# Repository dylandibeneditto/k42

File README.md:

<h1 align="center">K42</h1>

### Features
- **Wireless** BLE
- Onboard **Haptic Feedback**
- **Aluminum** Plate and Rotary Knobs
- 2x **Rotary Encoders** (per half)
- 2x SSD1306 **OLED** (per half)
- Reversible PCB
- **Hotswappable Choc** switches

### Purchasing
- Planning on a **DIY kit** for $150

> **One prototype for me cost ~$250**, so buying the kit saves a significant amount

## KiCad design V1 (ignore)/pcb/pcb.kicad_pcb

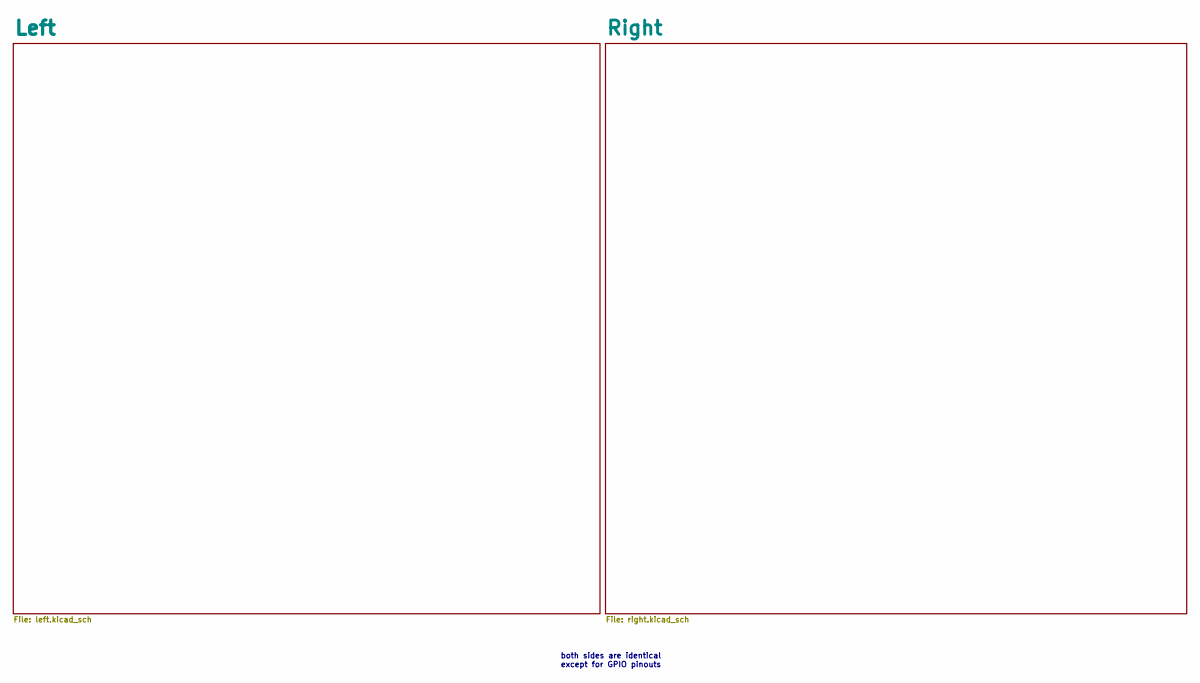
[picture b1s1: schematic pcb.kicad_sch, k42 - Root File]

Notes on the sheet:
both sides are identical except for GPIO pinouts

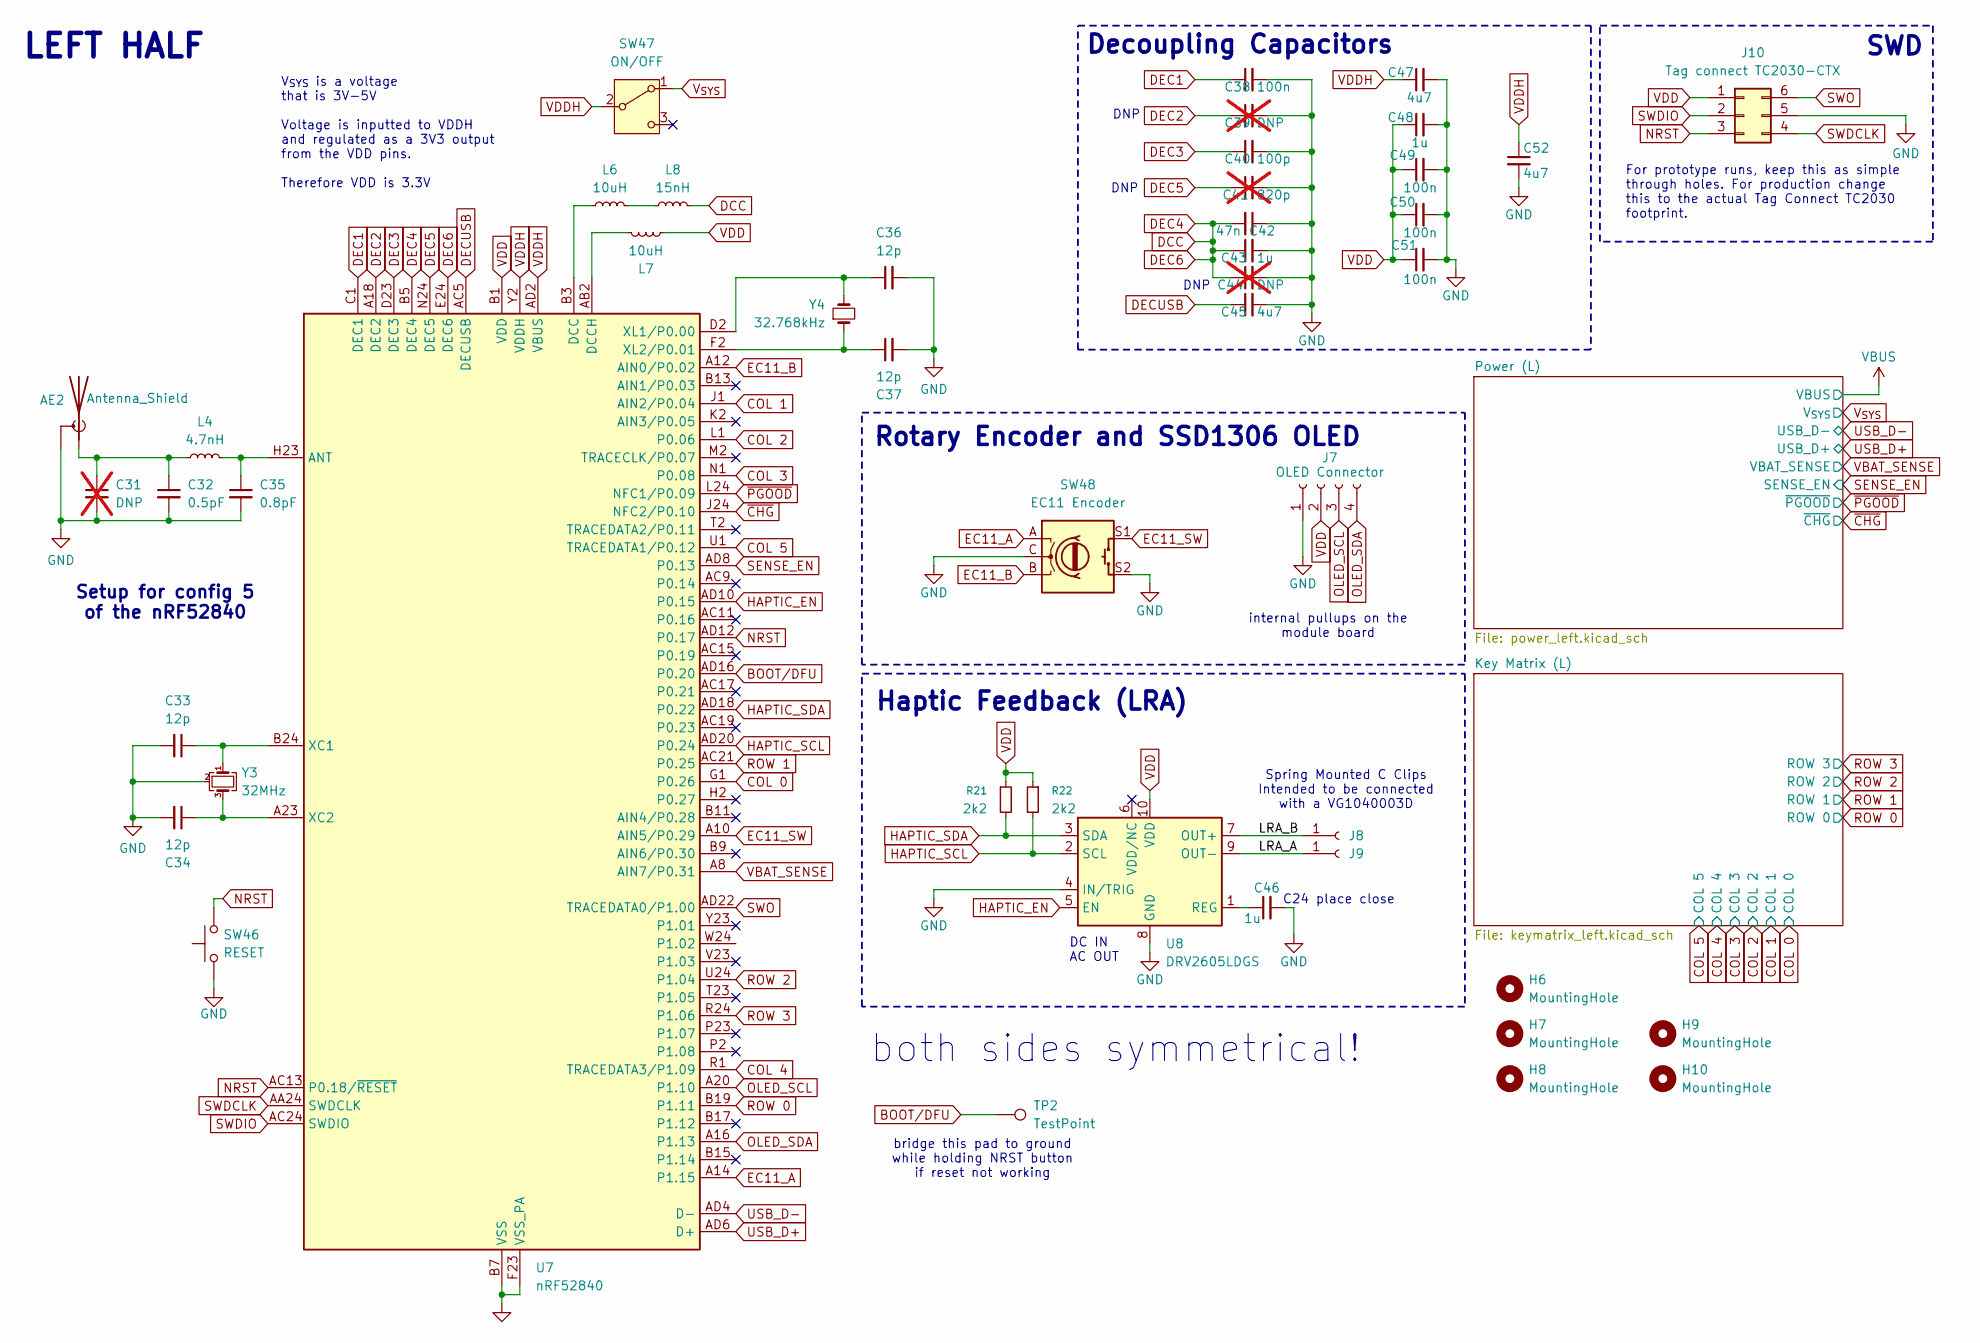
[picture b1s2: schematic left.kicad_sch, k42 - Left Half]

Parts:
AE2: Antenna_Shield; BLE_ANTENNA
C31, C39, C44: DNP; C_0402_1005Metric; not fitted
C32: 0.5pF; C_0402_1005Metric; LCSC Part Number C1544
C33, C34, C36, C37: 12p; C_0402_1005Metric; LCSC Part Number C1547
C35: 0.8pF; C_0402_1005Metric; LCSC Part Number C88902
C38, C49, C50, C51: 100n; C_0402_1005Metric; LCSC Part Number C1525
C40: 100p; C_0402_1005Metric; LCSC Part Number C1546
C41: 820p; C_0402_1005Metric; LCSC Part Number C1543; not fitted
C42: 47n; C_0402_1005Metric; LCSC Part Number C82219
C43, C46, C48: 1u; C_0603_1608Metric; LCSC Part Number C15849
C45, C47, C52: 4u7; C_0805_2012Metric; LCSC Part Number C1779
H6, H7, H8, H9, H10: MountingHole; MountingHole_2.2mm_M2
J7: OLED Connector; OLED
J8, J9: Conn_01x01_Socket; TE_2199248-6; LCSC Part Number C3308715
J10: Tag connect TC2030-CTX; PinHeader_2x03_P2.54mm_Vertical
L4: 4.7nH; L_0402_1005Metric; LCSC Part Number C86065
L6, L7: 10uH; L_0603_1608Metric; LCSC Part Number C1035
L8: 15nH; L_0402_1005Metric; LCSC Part Number C86059
R21, R22: 2k2; R_0402_1005Metric; LCSC Part Number C25879
SW46: RESET; SW_Push_SPST_NO_Alps_SKRK; LCSC Part Number C720477
SW47: ON/OFF; SW_SPDT_CK_JS102011SAQN; LCSC Part Number C49023767
SW48: EC11 Encoder; RotaryEncoder_Alps_EC11E-Switch_Vertical_H20mm_MountingHoles
TP2: TestPoint; TestPoint_Pad_2.0x2.0mm
U7: nRF52840; Nordic_AQFN-73-1EP_7x7mm_P0.5mm; LCSC Part Number C190794
U8: DRV2605LDGS; VSSOP-10_3x3mm_P0.5mm; LCSC Part Number C527464
Y3: 32MHz; Crystal_SMD_3225-4Pin_3.2x2.5mm; LCSC Part Number C9009
Y4: 32.768kHz; Crystal_SMD_3215-2Pin_3.2x1.5mm; LCSC Part Number C32346

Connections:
/Left/LRA_A: J9.1 (Pin_1_1), U8.9 (OUT-)
/Left/LRA_B: J8.1 (1_1), U8.7 (OUT+)
BOOT/DFU: TP2.1 (1_1), U7.AD16 (P0.20); also elsewhere on the board
COL 0: U7.G1 (P0.26); also elsewhere on the board
COL 1: U7.J1 (AIN2/P0.04); also elsewhere on the board
COL 2: U7.L1 (P0.06); also elsewhere on the board
COL 3: U7.N1 (P0.08); also elsewhere on the board
COL 4: U7.R1 (TRACEDATA3/P1.09); also elsewhere on the board
COL 5: U7.U1 (TRACEDATA1/P0.12); also elsewhere on the board
DCC: C42.2, C43.1, C44.1, L8.2, U7.B5 (DEC4), U7.E24 (DEC6); also elsewhere on the board
DEC3: C40.1, U7.D23 (DEC3); also elsewhere on the board
DECUSB: C45.1, U7.AC5 (DECUSB); also elsewhere on the board
EC11_A: SW48.A, U7.A14 (P1.15); also elsewhere on the board
EC11_B: SW48.B, U7.A12 (AIN0/P0.02); also elsewhere on the board
EC11_SW: SW48.S1, U7.A10 (AIN5/P0.29); also elsewhere on the board
GND: AE2.2 (Shield), C31.2, C32.2, C33.2, C34.2, C35.2, C36.2, C37.2, C38.2, C39.2, C40.2, C41.2, C42.1, C43.2, C44.2, C45.2, C46.2, C47.2, C48.2, C49.2, C50.2, C51.2, C52.2, J7.1, J10.5, SW46.1, SW48.C, SW48.S2, U7.B7 (VSS), U7.EP (VSS), U7.F23 (VSS_PA), U8.4 (IN/TRIG), U8.8 (GND), Y3.2 (G), Y3.4 (G); also elsewhere on the board
HAPTIC_EN: U7.AD10 (P0.15), U8.5 (EN); also elsewhere on the board
HAPTIC_SCL: R22.2, U7.AD20 (P0.24), U8.2 (SCL); also elsewhere on the board
HAPTIC_SDA: R21.2, U7.AD18 (P0.22), U8.3 (SDA); also elsewhere on the board
NRST: J10.3, SW46.2, U7.AC13 (P0.18/~RESET), U7.AD12 (P0.17); also elsewhere on the board
unnamed: AE2.1 (A), C31.1, C32.1, L4.1
unnamed: L6.2, L8.1
unnamed: C35.1, L4.2, U7.H23 (ANT)
unnamed: L6.1, U7.B3 (DCC)
unnamed: L7.1, U7.AB2 (DCCH)
unnamed: C33.1, U7.B24 (XC1), Y3.1
unnamed: C34.1, U7.A23 (XC2), Y3.3
unnamed: C36.1, U7.D2 (XL1/P0.00), Y4.2
unnamed: C37.1, U7.F2 (XL2/P0.01), Y4.1
unnamed: C46.1, U8.1 (REG)
OLED_SCL: J7.3, U7.A20 (P1.10); also elsewhere on the board
OLED_SDA: J7.4, U7.A16 (P1.13); also elsewhere on the board
ROW 0: U7.B19 (P1.11); also elsewhere on the board
ROW 1: U7.AC21 (P0.25); also elsewhere on the board
ROW 2: U7.U24 (P1.04); also elsewhere on the board
ROW 3: U7.R24 (P1.06); also elsewhere on the board
SENSE_EN: U7.AD8 (P0.13); also elsewhere on the board
SWDCLK: J10.4, U7.AA24 (SWDCLK); also elsewhere on the board
SWDIO: J10.2, U7.AC24 (SWDIO); also elsewhere on the board
SWO: J10.6, U7.AD22 (TRACEDATA0/P1.00); also elsewhere on the board
USB_D+: U7.AD6 (D+); also elsewhere on the board
USB_D-: U7.AD4 (D-); also elsewhere on the board
VBAT_SENSE: U7.A8 (AIN7/P0.31); also elsewhere on the board
VDD: C48.1, C49.1, C50.1, C51.1, J7.2, J10.1, L7.2, R21.1, R22.1, U7.A22 (VDD), U7.AD14 (VDD), U7.AD23 (VDD), U7.B1 (VDD), U7.W1 (VDD), U8.10 (VDD); also elsewhere on the board
VDDH: C47.1, C52.1, SW47.2 (B), U7.AD2 (VBUS), U7.Y2 (VDDH); also elsewhere on the board
V_{SYS}: SW47.1 (A); also elsewhere on the board
~CHG: U7.J24 (NFC2/P0.10); also elsewhere on the board
~PGOOD: U7.L24 (NFC1/P0.09); also elsewhere on the board

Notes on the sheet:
DC IN AC OUT
DNP
LEFT HALF
For prototype runs, keep this as simple through holes. For production change this to the actual Tag Connect TC2030 footprint.
Spring Mounted C Clips Intended to be connected with a VG1040003D
bridge this pad to ground while holding NRST button if reset not working
internal pullups on the module board
V_{SYS} is a voltage that is 3V-5V Voltage is inputted to VDDH and regulated as a 3V3 output from the VDD pins. Therefore VDD is 3.3V
SWD
both sides symmetrical!
C24 place close
Decoupling Capacitors
Rotary Encoder and SSD1306 OLED
Haptic Feedback (LRA)
Setup for config 5 of the nRF52840

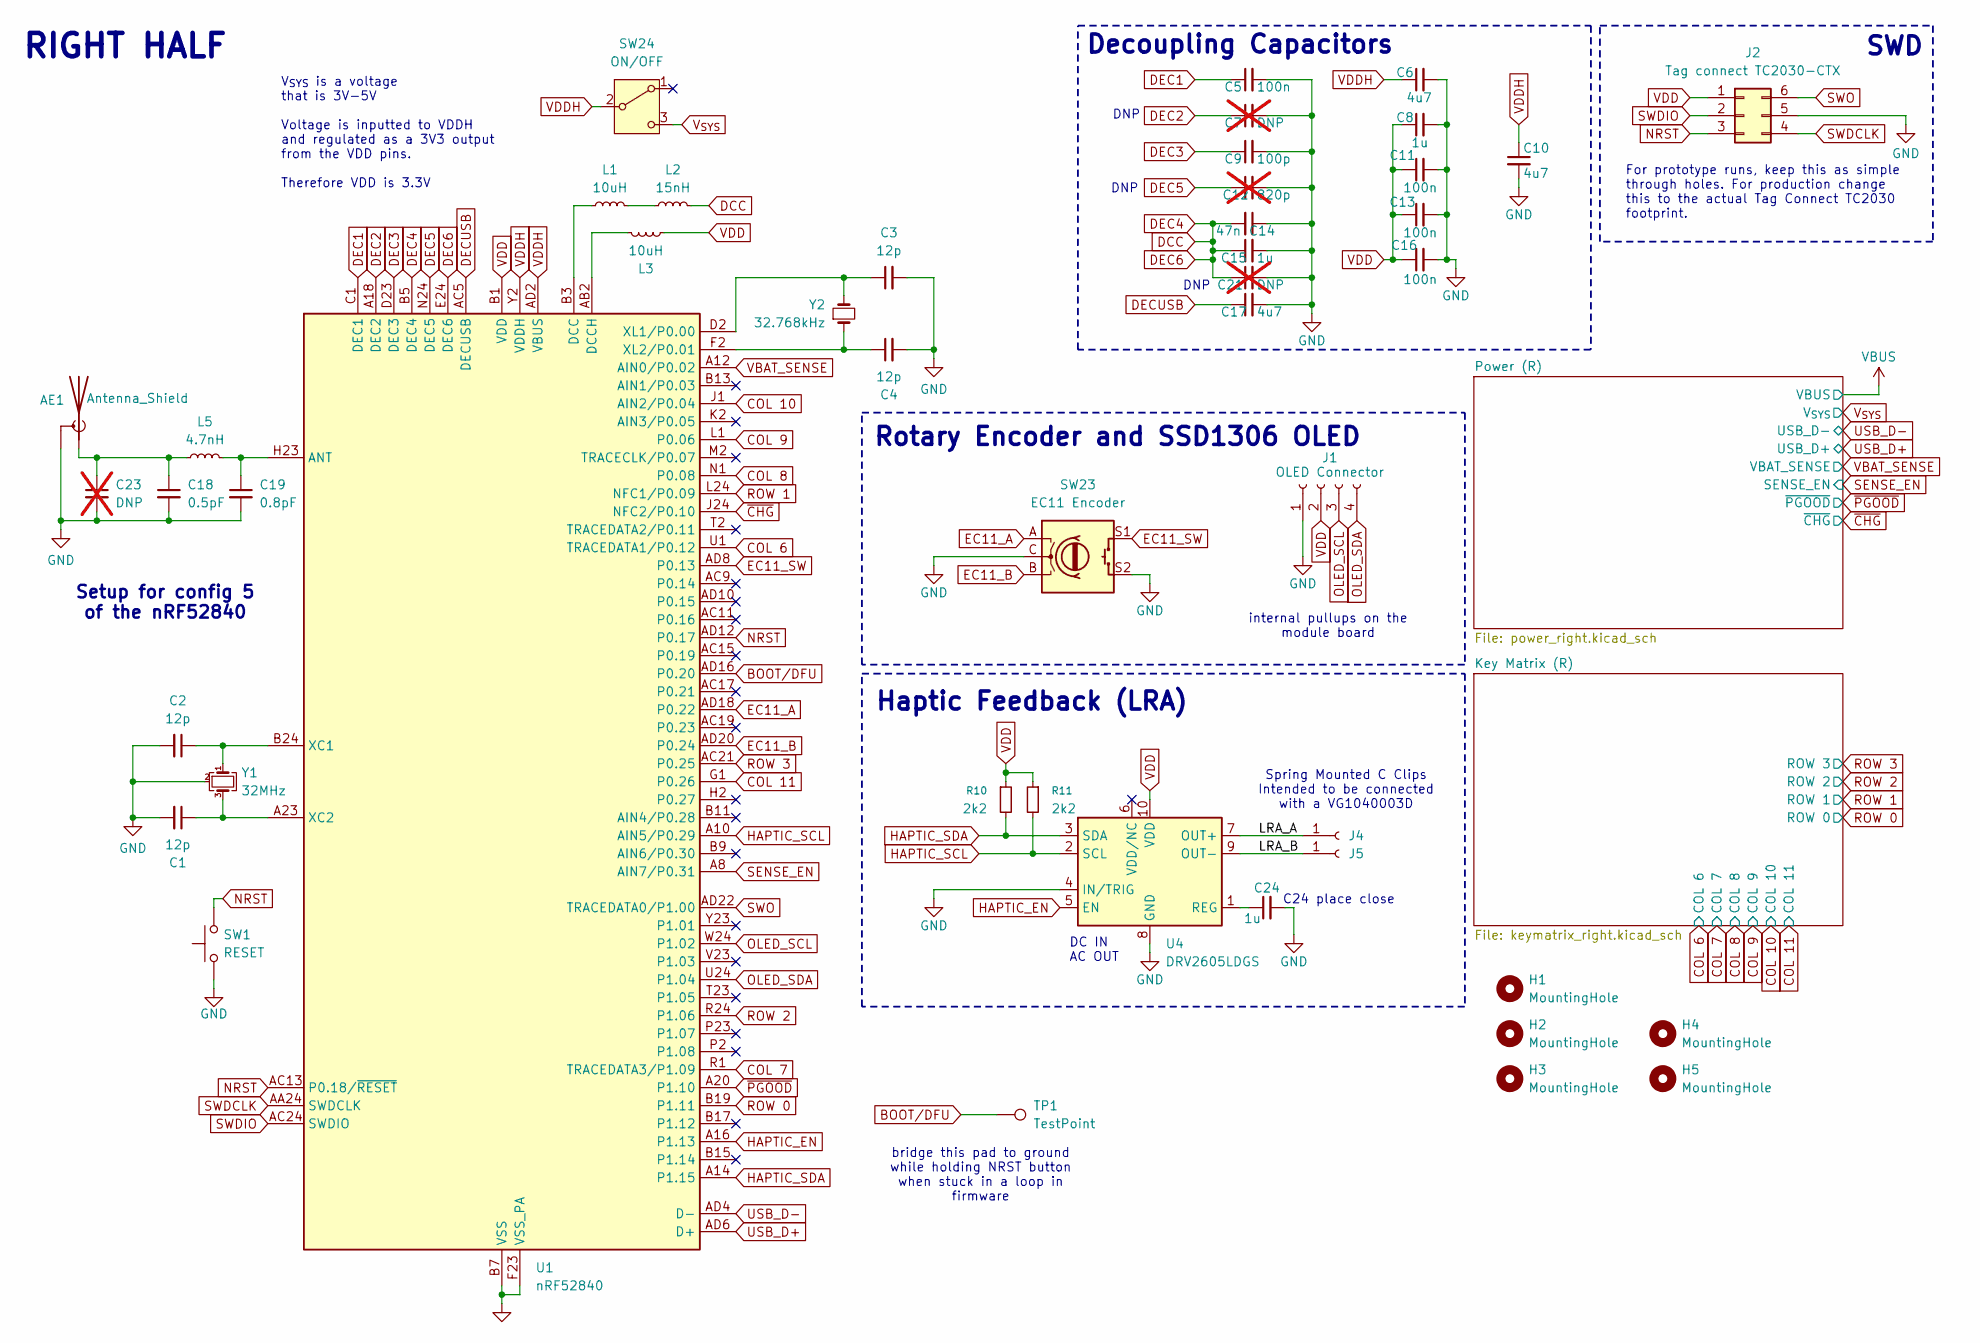
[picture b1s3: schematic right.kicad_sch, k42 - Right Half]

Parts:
AE1: Antenna_Shield; BLE_ANTENNA
C1, C2, C3, C4: 12p; C_0402_1005Metric; LCSC Part Number C1547
C5, C11, C13, C16: 100n; C_0402_1005Metric; LCSC Part Number C1525
C6, C10, C17: 4u7; C_0805_2012Metric; LCSC Part Number C1779
C7, C21, C23: DNP; C_0402_1005Metric; not fitted
C8, C15, C24: 1u; C_0603_1608Metric; LCSC Part Number C15849
C9: 100p; C_0402_1005Metric; LCSC Part Number C1546
C12: 820p; C_0402_1005Metric; LCSC Part Number C1543; not fitted
C14: 47n; C_0402_1005Metric; LCSC Part Number C82219
C18: 0.5pF; C_0402_1005Metric; LCSC Part Number C1544
C19: 0.8pF; C_0402_1005Metric; LCSC Part Number C88902
H1, H2, H3, H4, H5: MountingHole; MountingHole_2.2mm_M2
J1: OLED Connector; OLED
J2: Tag connect TC2030-CTX; PinHeader_2x03_P2.54mm_Vertical
J4, J5: Conn_01x01_Socket; TE_2199248-6; LCSC Part Number C3308715
L1, L3: 10uH; L_0603_1608Metric; LCSC Part Number C1035
L2: 15nH; L_0402_1005Metric; LCSC Part Number C86059
L5: 4.7nH; L_0402_1005Metric; LCSC Part Number C86065
R10, R11: 2k2; R_0402_1005Metric; LCSC Part Number C25879
SW1: RESET; SW_Push_SPST_NO_Alps_SKRK; LCSC Part Number C720477
SW23: EC11 Encoder; RotaryEncoder_Alps_EC11E-Switch_Vertical_H20mm_MountingHoles
SW24: ON/OFF; SW_SPDT_CK_JS102011SAQN; LCSC Part Number C49023767
TP1: TestPoint; TestPoint_Pad_2.0x2.0mm
U1: nRF52840; Nordic_AQFN-73-1EP_7x7mm_P0.5mm; LCSC Part Number C190794
U4: DRV2605LDGS; VSSOP-10_3x3mm_P0.5mm; LCSC Part Number C527464
Y1: 32MHz; Crystal_SMD_3225-4Pin_3.2x2.5mm; LCSC Part Number C9009
Y2: 32.768kHz; Crystal_SMD_3215-2Pin_3.2x1.5mm; LCSC Part Number C32346

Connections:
/Right/LRA_A: J4.1 (1_1), U4.7 (OUT+); also elsewhere on the board
/Right/LRA_B: J5.1 (Pin_1_1), U4.9 (OUT-); also elsewhere on the board
BOOT/DFU: TP1.1 (1_1), U1.AD16 (P0.20); also elsewhere on the board
COL 6: U1.U1 (TRACEDATA1/P0.12); also elsewhere on the board
COL 7: U1.R1 (TRACEDATA3/P1.09); also elsewhere on the board
COL 8: U1.N1 (P0.08); also elsewhere on the board
COL 9: U1.L1 (P0.06); also elsewhere on the board
COL 10: U1.J1 (AIN2/P0.04); also elsewhere on the board
COL 11: U1.G1 (P0.26); also elsewhere on the board
DCC: C14.2, C15.1, L2.2, U1.B5 (DEC4), U1.E24 (DEC6); also elsewhere on the board
DEC3: C9.1, U1.D23 (DEC3); also elsewhere on the board
DECUSB: C17.1, U1.AC5 (DECUSB); also elsewhere on the board
EC11_A: SW23.A, U1.AD18 (P0.22); also elsewhere on the board
EC11_B: SW23.B, U1.AD20 (P0.24); also elsewhere on the board
EC11_SW: SW23.S1, U1.AD8 (P0.13); also elsewhere on the board
GND: AE1.2 (Shield), C1.2, C2.2, C3.2, C4.2, C5.2, C6.2, C8.2, C9.2, C10.2, C11.2, C13.2, C14.1, C15.2, C16.2, C17.2, C18.2, C19.2, C24.2, J1.1, J2.5, SW1.1, SW23.C, SW23.S2, U1.B7 (VSS), U1.EP (VSS), U1.F23 (VSS_PA), U4.4 (IN/TRIG), U4.8 (GND), Y1.2 (G), Y1.4 (G); also elsewhere on the board
HAPTIC_EN: U1.A16 (P1.13), U4.5 (EN); also elsewhere on the board
HAPTIC_SCL: R11.2, U1.A10 (AIN5/P0.29), U4.2 (SCL); also elsewhere on the board
HAPTIC_SDA: R10.2, U1.A14 (P1.15), U4.3 (SDA); also elsewhere on the board
NRST: J2.3, SW1.2, U1.AC13 (P0.18/~RESET), U1.AD12 (P0.17); also elsewhere on the board
unnamed: L1.2, L2.1
unnamed: C19.1, L5.2, U1.H23 (ANT)
unnamed: L1.1, U1.B3 (DCC)
unnamed: L3.1, U1.AB2 (DCCH)
unnamed: C1.1, U1.A23 (XC2), Y1.3
unnamed: C3.1, U1.D2 (XL1/P0.00), Y2.2
unnamed: C4.1, U1.F2 (XL2/P0.01), Y2.1
OLED_SCL: J1.3, U1.W24 (P1.02); also elsewhere on the board
OLED_SDA: J1.4, U1.U24 (P1.04); also elsewhere on the board
ROW 1: U1.L24 (NFC1/P0.09); also elsewhere on the board
ROW 2: U1.R24 (P1.06); also elsewhere on the board
ROW 3: U1.AC21 (P0.25); also elsewhere on the board
SENSE_EN: U1.A8 (AIN7/P0.31); also elsewhere on the board
SWDCLK: J2.4, U1.AA24 (SWDCLK); also elsewhere on the board
SWDIO: J2.2, U1.AC24 (SWDIO); also elsewhere on the board
SWO: J2.6, U1.AD22 (TRACEDATA0/P1.00); also elsewhere on the board
USB_D+: U1.AD6 (D+); also elsewhere on the board
USB_D-: U1.AD4 (D-); also elsewhere on the board
VBAT_SENSE: U1.A12 (AIN0/P0.02); also elsewhere on the board
VDD: C8.1, C11.1, C13.1, C16.1, J1.2, J2.1, L3.2, R10.1, R11.1, U1.A22 (VDD), U1.AD14 (VDD), U1.AD23 (VDD), U1.B1 (VDD), U1.W1 (VDD), U4.10 (VDD); also elsewhere on the board
VDDH: C6.1, C10.1, SW24.2 (B), U1.AD2 (VBUS), U1.Y2 (VDDH); also elsewhere on the board
V_{SYS}: SW24.3 (C); also elsewhere on the board
~CHG: U1.B19 (P1.11), U1.J24 (NFC2/P0.10); also elsewhere on the board
~PGOOD: U1.A20 (P1.10); also elsewhere on the board

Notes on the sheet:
bridge this pad to ground while holding NRST button when stuck in a loop in firmware
SWD
DNP
RIGHT HALF
V_{SYS} is a voltage that is 3V-5V Voltage is inputted to VDDH and regulated as a 3V3 output from the VDD pins. Therefore VDD is 3.3V
Setup for config 5 of the nRF52840
Haptic Feedback (LRA)
Spring Mounted C Clips Intended to be connected with a VG1040003D
For prototype runs, keep this as simple through holes. For production change this to the actual Tag Connect TC2030 footprint.
Decoupling Capacitors
internal pullups on the module board
Rotary Encoder and SSD1306 OLED
DC IN AC OUT
C24 place close

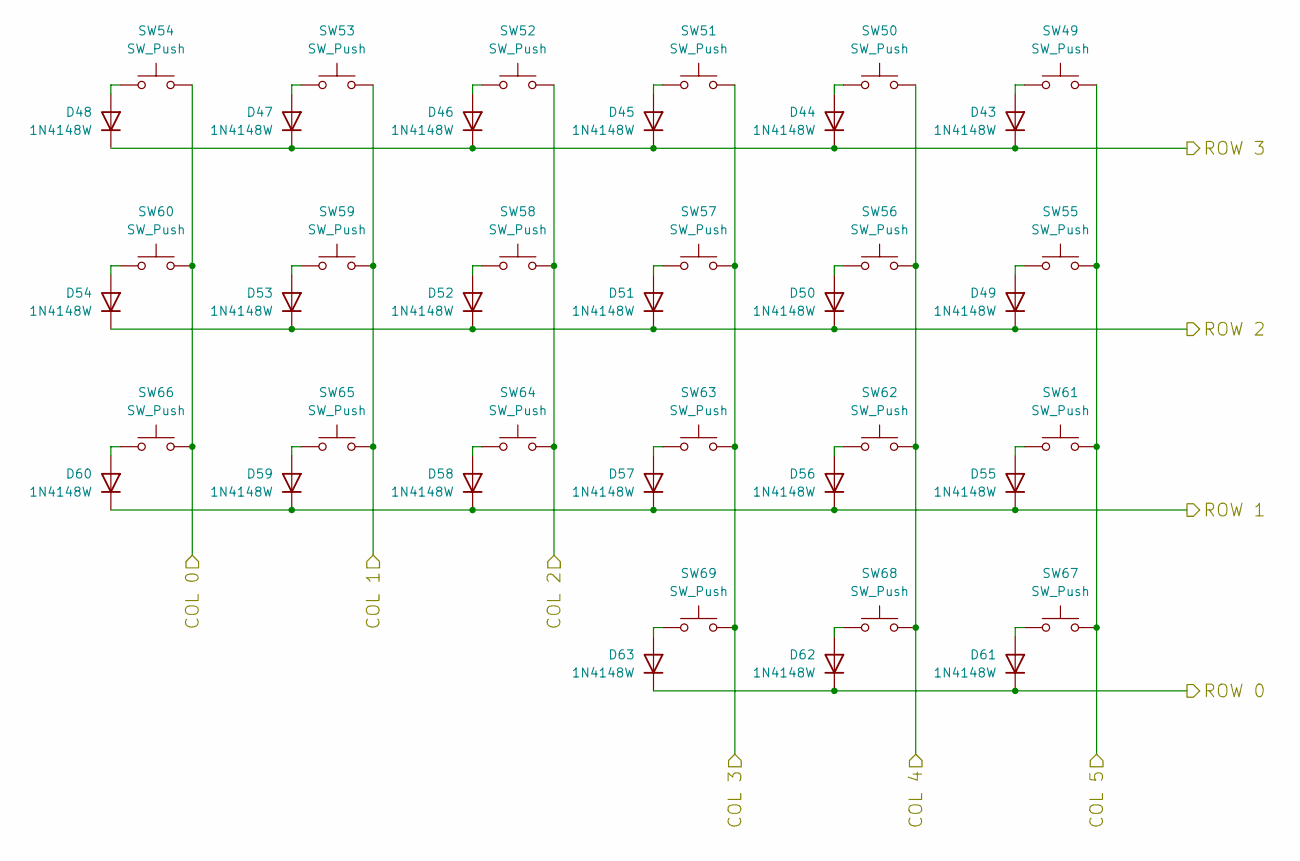
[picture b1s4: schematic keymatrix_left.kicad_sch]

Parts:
D43, D44, D45, D46, D47, D48, D49, D50, D51, D52, D53, D54, D55, D56, D57, D58, D59, D60, D61, D62, D63: 1N4148W; D_SOD-123; LCSC Part Number C2128
SW49, SW50, SW51, SW52, SW53, SW54, SW55, SW56, SW57, SW58, SW59, SW60, SW61, SW62, SW63, SW64, SW65, SW66, SW67, SW68, SW69: SW_Push; keyswitch_choc12_hotswap_1u; LCSC Part Number C5184526

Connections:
COL 0: SW54.1, SW60.1, SW66.1; also elsewhere on the board
COL 1: SW53.1, SW59.1, SW65.1; also elsewhere on the board
COL 2: SW52.1, SW58.1, SW64.1; also elsewhere on the board
COL 3: SW51.1, SW57.1, SW63.1, SW69.1; also elsewhere on the board
COL 4: SW50.1, SW56.1, SW62.1, SW68.1; also elsewhere on the board
COL 5: SW49.1, SW55.1, SW61.1, SW67.1; also elsewhere on the board
unnamed: D43.2 (A), SW49.2
unnamed: D44.2 (A), SW50.2
unnamed: D45.2 (A), SW51.2
unnamed: D46.2 (A), SW52.2
unnamed: D47.2 (A), SW53.2
unnamed: D48.2 (A), SW54.2
unnamed: D49.2 (A), SW55.2
unnamed: D50.2 (A), SW56.2
unnamed: D51.2 (A), SW57.2
unnamed: D52.2 (A), SW58.2
unnamed: D53.2 (A), SW59.2
unnamed: D54.2 (A), SW60.2
unnamed: D55.2 (A), SW61.2
unnamed: D56.2 (A), SW62.2
unnamed: D57.2 (A), SW63.2
unnamed: D58.2 (A), SW64.2
unnamed: D59.2 (A), SW65.2
unnamed: D60.2 (A), SW66.2
unnamed: D61.2 (A), SW67.2
unnamed: D62.2 (A), SW68.2
unnamed: D63.2 (A), SW69.2
ROW 0: D61.1 (K), D62.1 (K), D63.1 (K); also elsewhere on the board
ROW 1: D55.1 (K), D56.1 (K), D57.1 (K), D58.1 (K), D59.1 (K), D60.1 (K); also elsewhere on the board
ROW 2: D49.1 (K), D50.1 (K), D51.1 (K), D52.1 (K), D53.1 (K), D54.1 (K); also elsewhere on the board
ROW 3: D43.1 (K), D44.1 (K), D45.1 (K), D46.1 (K), D47.1 (K), D48.1 (K); also elsewhere on the board

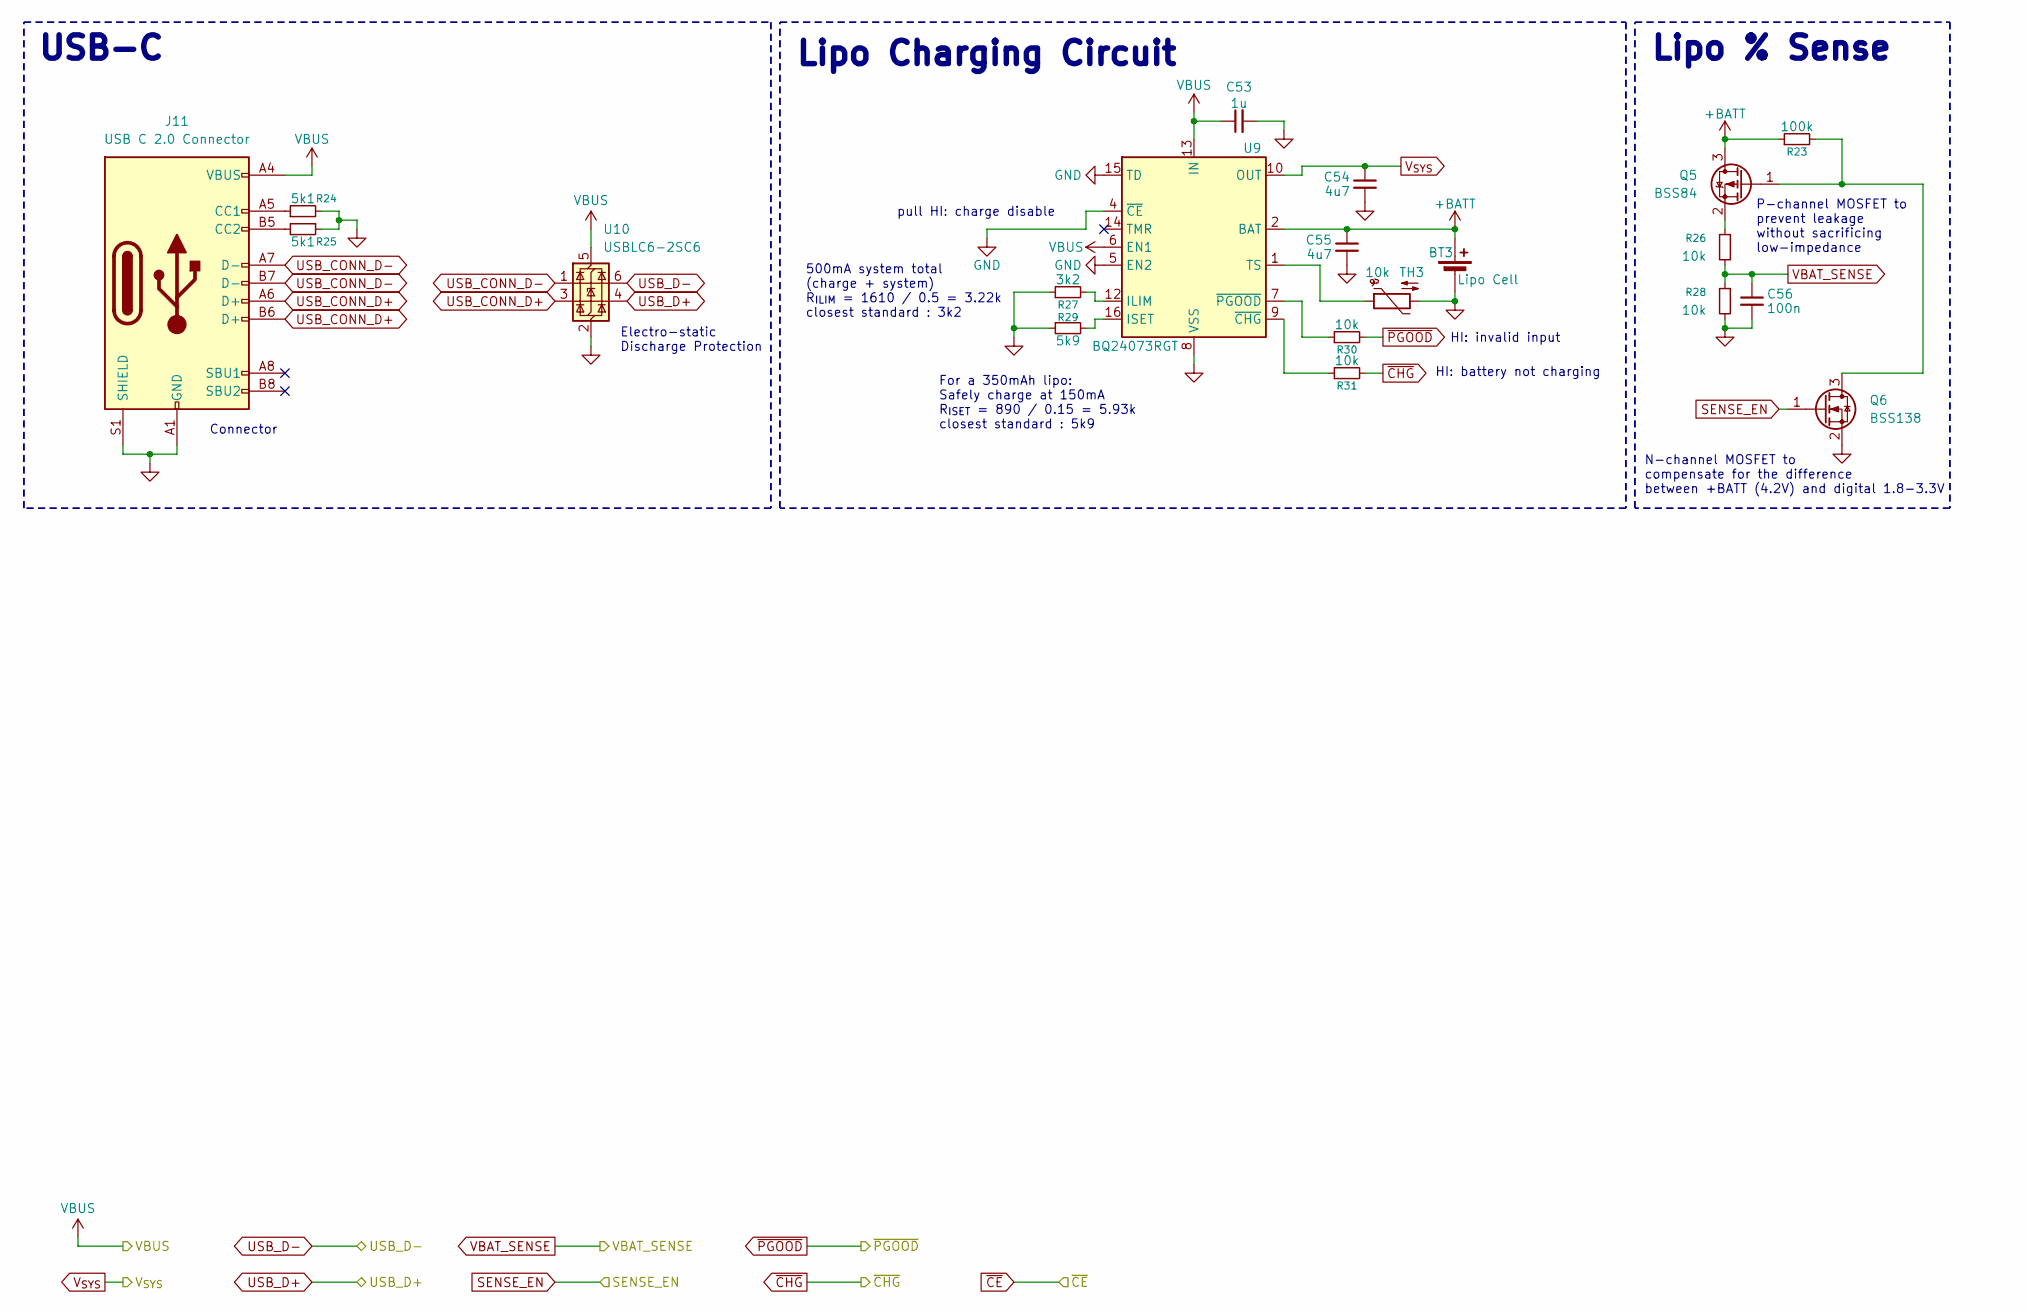
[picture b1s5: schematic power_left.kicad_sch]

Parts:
BT3: Lipo Cell; JST_PH_S2B-PH-SM4-TB_1x02-1MP_P2.00mm_Horizontal; LCSC Part Number C295747
C53: 1u; C_0603_1608Metric; LCSC Part Number C15849
C54, C55: 4u7; C_0805_2012Metric; LCSC Part Number C1779
C56: 100n; C_0402_1005Metric; LCSC Part Number C1525
J11: USB C 2.0 Connector; TYPE-C-31-M-13C; LCSC Part Number C2765186
Q5: BSS84; SOT-23; LCSC Part Number C8492
Q6: BSS138; SOT-23; LCSC Part Number C8490
R23: 100k; R_0603_1608Metric; LCSC Part Number C25803
R24, R25: 5k1; R_0402_1005Metric; LCSC Part Number C17168
R26, R28, R30, R31: 10k; R_0402_1005Metric; LCSC Part Number C60490
R27: 3k2; R_0402_1005Metric; LCSC Part Number C705066
R29: 5k9; R_0402_1005Metric; LCSC Part Number C166634
TH3: 10k; R_0402_1005Metric; LCSC Part Number C209959
U9: BQ24073RGT; VQFN-16-1EP_3x3mm_P0.5mm_EP1.6x1.6mm; LCSC Part Number C15220
U10: USBLC6-2SC6; SOT-23-6; LCSC Part Number C2687116

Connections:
+BATT: BT3.1 (+), C55.1, Q5.3 (D), R23.1, U9.2 (BAT), U9.3 (BAT); also elsewhere on the board
GND: BT3.2 (-), C53.2, C54.2, C55.2, C56.2, J11.A1 (GND), J11.A12 (GND), J11.B1 (GND), J11.B12 (GND), J11.S1 (SHIELD), Q6.2 (S), R24.2, R25.1, R27.1, R28.2, R29.1, TH3.2, U9.4 (~CE), U9.5 (EN2), U9.8 (VSS), U9.15 (TD), U9.17 (VSS), U10.2 (GND); also elsewhere on the board
unnamed: J11.A5 (CC1), R24.1
unnamed: J11.B5 (CC2), R25.2
unnamed: Q5.1 (G), Q6.3 (D), R23.2
unnamed: Q5.2 (S), R26.1
unnamed: R27.2, U9.12 (ILIM)
unnamed: R29.2, U9.16 (ISET)
unnamed: TH3.1, U9.1 (TS)
unnamed: R31.1, U9.9 (~CHG)
unnamed: R30.1, U9.7 (~PGOOD)
SENSE_EN: Q6.1 (G); also elsewhere on the board
USB_CONN_D+: J11.A6 (D+), J11.B6 (D+), U10.3 (I/O2); also elsewhere on the board
USB_CONN_D-: J11.A7 (D-), J11.B7 (D-), U10.1 (I/O1); also elsewhere on the board
USB_D+: U10.4 (I/O2); also elsewhere on the board
USB_D-: U10.6 (I/O1); also elsewhere on the board
VBAT_SENSE: C56.1, R26.2, R28.1; also elsewhere on the board
VBUS: C53.1, J11.A4 (VBUS), J11.A9 (VBUS), J11.B4 (VBUS), J11.B9 (VBUS), U9.6 (EN1), U9.13 (IN), U10.5 (VBUS); also elsewhere on the board
V_{SYS}: C54.1, U9.10 (OUT), U9.11 (OUT); also elsewhere on the board
~CHG: R31.2; also elsewhere on the board
~PGOOD: R30.2; also elsewhere on the board

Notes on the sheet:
Connector
Lipo % Sense
Lipo Charging Circuit
pull HI: charge disable
P-channel MOSFET to prevent leakage without sacrificing low-impedance
500mA system total (charge + system) R_{ILIM} = 1610 / 0.5 = 3.22k closest standard : 3k2
USB-C
HI: battery not charging
N-channel MOSFET to compensate for the difference between +BATT (4.2V) and digital 1.8-3.3V
For a 350mAh lipo: Safely charge at 150mA R_{ISET} = 890 / 0.15 = 5.93k closest standard : 5k9
HI: invalid input
Electro-static Discharge Protection

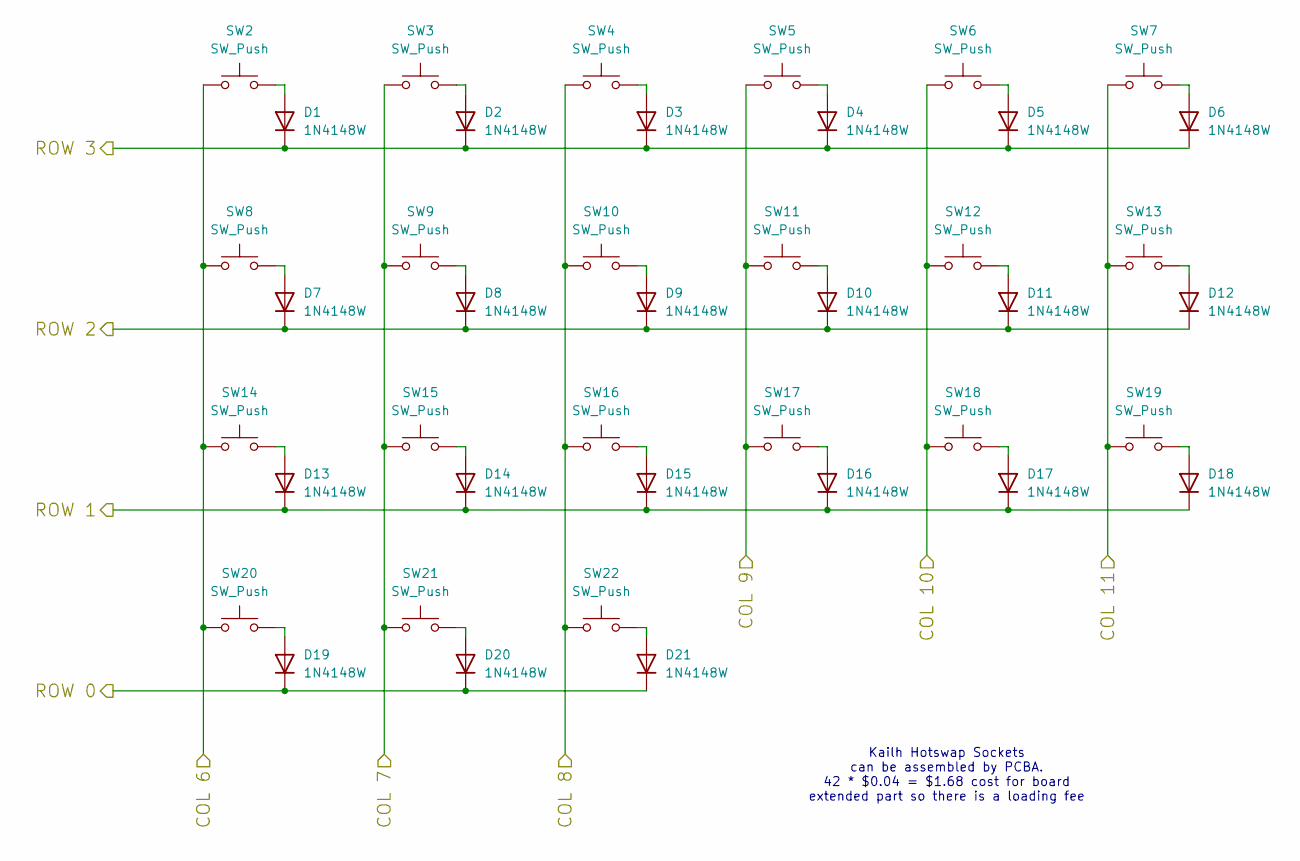
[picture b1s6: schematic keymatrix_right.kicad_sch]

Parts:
D1, D2, D3, D4, D5, D6, D7, D8, D9, D10, D11, D12, D13, D14, D15, D16, D17, D18, D19, D20, D21: 1N4148W; D_SOD-123; LCSC Part Number C2128
SW2, SW3, SW4, SW5, SW6, SW7, SW8, SW9, SW10, SW11, SW12, SW13, SW14, SW15, SW16, SW17, SW18, SW19, SW20, SW21, SW22: SW_Push; keyswitch_choc12_hotswap_1u; LCSC Part Number C5184526

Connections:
COL 6: SW2.1, SW8.1, SW14.1, SW20.1; also elsewhere on the board
COL 7: SW3.1, SW9.1, SW15.1, SW21.1; also elsewhere on the board
COL 8: SW4.1, SW10.1, SW16.1, SW22.1; also elsewhere on the board
COL 9: SW5.1, SW11.1, SW17.1; also elsewhere on the board
COL 10: SW6.1, SW12.1, SW18.1; also elsewhere on the board
COL 11: SW7.1, SW13.1, SW19.1; also elsewhere on the board
unnamed: D1.2 (A), SW2.2
unnamed: D2.2 (A), SW3.2
unnamed: D3.2 (A), SW4.2
unnamed: D4.2 (A), SW5.2
unnamed: D5.2 (A), SW6.2
unnamed: D6.2 (A), SW7.2
unnamed: D7.2 (A), SW8.2
unnamed: D8.2 (A), SW9.2
unnamed: D9.2 (A), SW10.2
unnamed: D10.2 (A), SW11.2
unnamed: D11.2 (A), SW12.2
unnamed: D12.2 (A), SW13.2
unnamed: D13.2 (A), SW14.2
unnamed: D14.2 (A), SW15.2
unnamed: D15.2 (A), SW16.2
unnamed: D16.2 (A), SW17.2
unnamed: D17.2 (A), SW18.2
unnamed: D18.2 (A), SW19.2
unnamed: D19.2 (A), SW20.2
unnamed: D20.2 (A), SW21.2
unnamed: D21.2 (A), SW22.2
ROW 0: D19.1 (K), D20.1 (K), D21.1 (K); also elsewhere on the board
ROW 1: D13.1 (K), D14.1 (K), D15.1 (K), D16.1 (K), D17.1 (K), D18.1 (K); also elsewhere on the board
ROW 2: D7.1 (K), D8.1 (K), D9.1 (K), D10.1 (K), D11.1 (K), D12.1 (K); also elsewhere on the board
ROW 3: D1.1 (K), D2.1 (K), D3.1 (K), D4.1 (K), D5.1 (K), D6.1 (K); also elsewhere on the board

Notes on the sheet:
Kailh Hotswap Sockets can be assembled by PCBA. 42 * $0.04 = $1.68 cost for board extended part so there is a loading fee
